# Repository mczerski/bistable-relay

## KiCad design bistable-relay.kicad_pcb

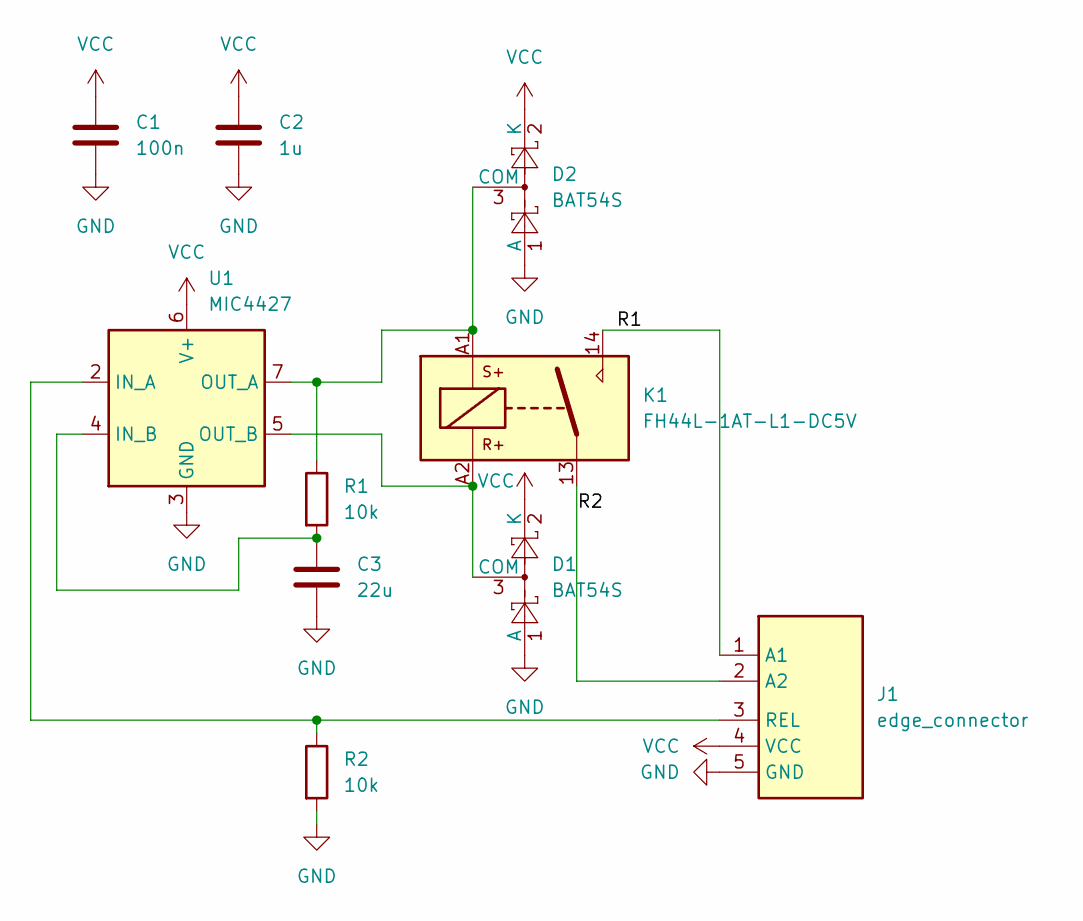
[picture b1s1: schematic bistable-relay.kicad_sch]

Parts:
C1: 100n; C_0402_1005Metric
C2: 1u; C_0603_1608Metric
C3: 22u; C_1206_3216Metric
D1, D2: BAT54S; SOT-23
J1: edge_connector
K1: FH44L-1AT-L1-DC5V; RELAY-TH_FH44L-1AT-L1-DC5V
R1, R2: 10k; R_0603_1608Metric
U1: MIC4427; SOIC-8_3.9x4.9mm_P1.27mm

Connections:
/R1: J1.1 (A1), K1.14
/R2: J1.2 (A2), K1.13
GND: C1.2, C2.2, C3.2, D1.1 (A), D2.1 (A), J1.5 (GND), R2.2, U1.3 (GND)
unnamed: D1.3 (COM), K1.A2, U1.5 (OUT_B)
unnamed: D2.3 (COM), K1.A1, R1.1, U1.7 (OUT_A)
unnamed: J1.3 (REL), R2.1, U1.2 (IN_A)
unnamed: C3.1, R1.2, U1.4 (IN_B)
VCC: C1.1, C2.1, D1.2 (K), D2.2 (K), J1.4 (VCC), U1.6 (V+)

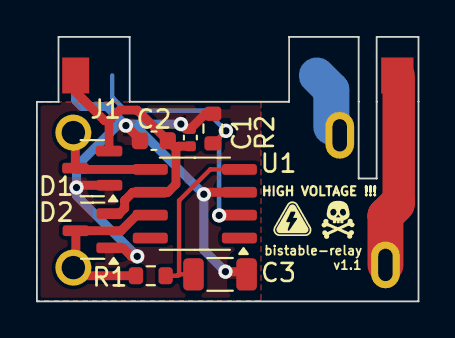
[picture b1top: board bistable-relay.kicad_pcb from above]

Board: 2 copper layers, 21.2 x 14.7 mm, 10 parts (1 on the bottom side), 8 nets.

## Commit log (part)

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2024-11-24 use FH44L relay
2024-11-26 move signal pads to bottom layer
2024-11-26 generate gerbers
2024-12-12 change 100nF capacitor to 0402 package
2024-12-16 add BOM
2025-01-01 add schematic in pdf
